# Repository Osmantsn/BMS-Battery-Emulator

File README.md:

# BMS-Test-Battery-Emulator
Hardware-based battery emulator for safe BMS testing. ESP32-S3 host controls up to 4 cell boards via I²C (AD5282), reads voltage/current/temperature through a multiplexer (ADG706), and provides a simple GUI/control interface.

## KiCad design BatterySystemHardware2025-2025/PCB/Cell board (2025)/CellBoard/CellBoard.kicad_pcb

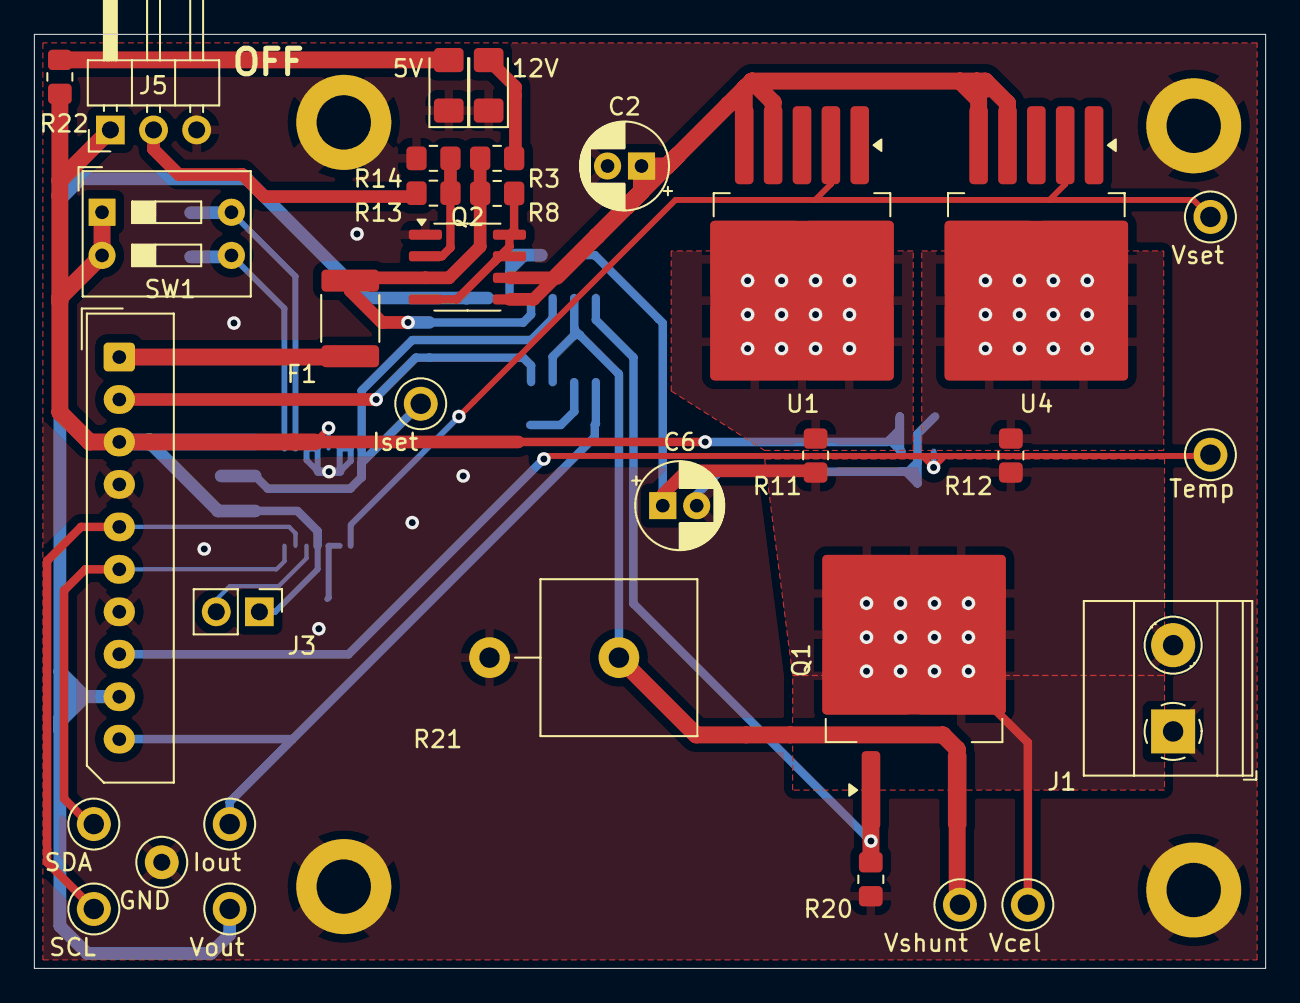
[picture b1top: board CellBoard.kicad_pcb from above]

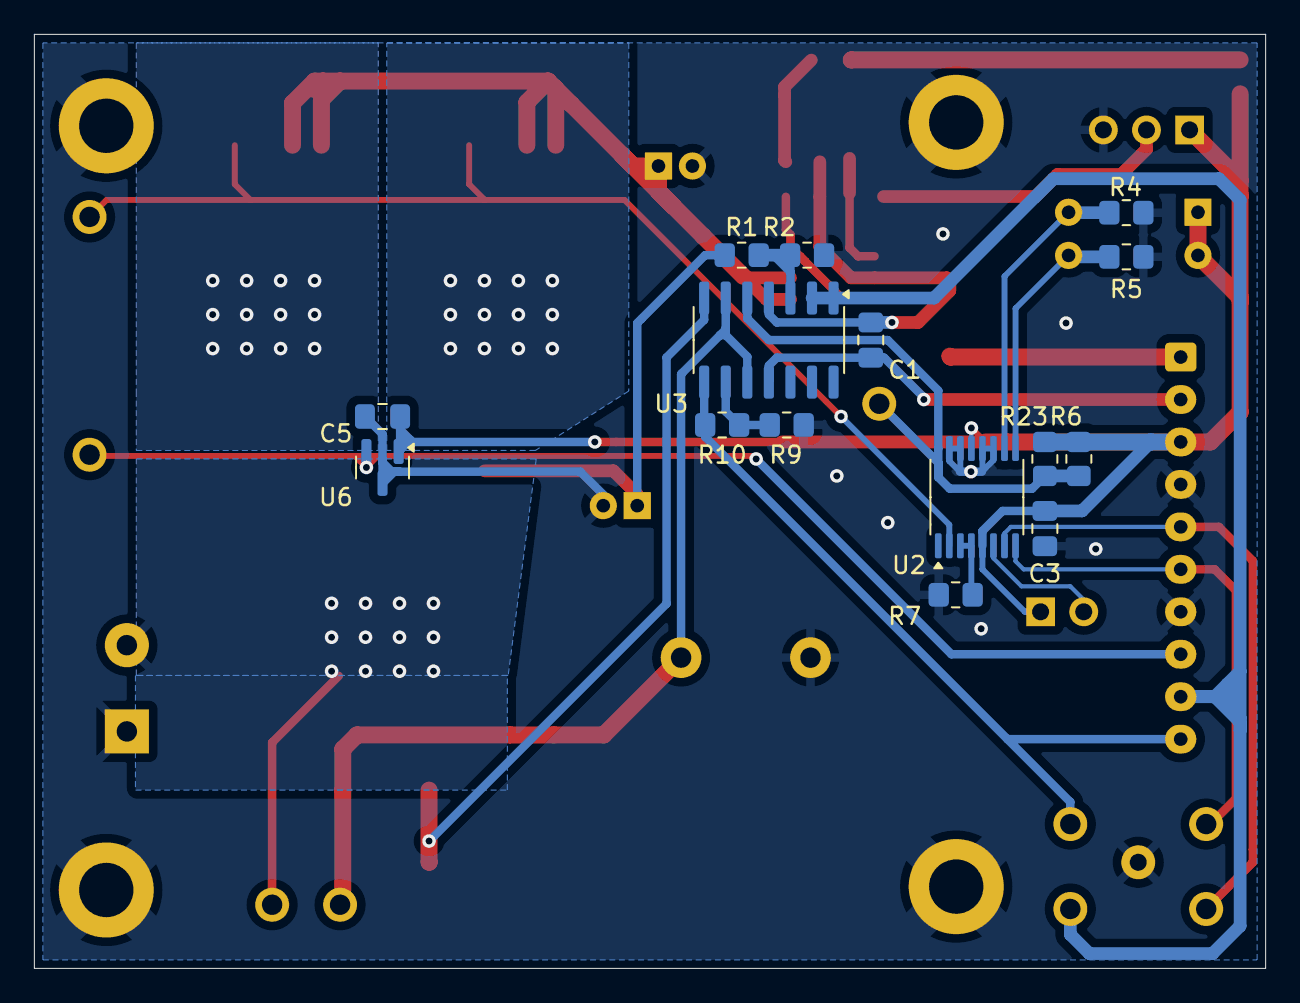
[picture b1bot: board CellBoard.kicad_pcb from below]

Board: 2 copper layers, 72.5 x 55.0 mm, 52 parts (15 on the bottom side), 29 nets.

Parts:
5V, 12V: LED; LED_1206_3216Metric_Pad1.42x1.75mm_HandSolder
C1, C3, C5: 100n; C_0805_2012Metric_Pad1.18x1.45mm_HandSolder
C2: 1u; CP_Radial_D5.0mm_P2.00mm
C6: 10u; CP_Radial_D5.0mm_P2.00mm
F1: 1812L200/12DR; Fuse_1812_4532Metric_Pad1.30x3.40mm_HandSolder
GND: TestPoint; TestPoint_Loop_D2.50mm_Drill1.0mm
H5, H6, H7, H8: MountingHole_Pad; MountingHole_3.2mm_M3_DIN965_Pad
Iout: TestPoint; TestPoint_Loop_D2.50mm_Drill1.0mm
Iset: TestPoint; TestPoint_Loop_D2.50mm_Drill1.0mm
J1: Screw_Terminal_01x02; TerminalBlock_Phoenix_MKDS-1,5-2-5.08_1x02_P5.08mm_Horizont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
J2: Conn_01x10_Pin; Molex_SPOX_5267-10A_1x10_P2.50mm_Vertical
J3: Conn_01x02_Pin; PinHeader_1x02_P2.54mm_Vertical
J5: Conn_01x03_Pin; PinHeader_1x03_P2.54mm_Horizontal
Q1: IRFS4115; TO-263-2
Q2: FDS4897C; SOIC-8_3.9x4.9mm_P1.27mm
R1: 1k2; R_0805_2012Metric_Pad1.20x1.40mm_HandSolder
R2: 2k7; R_0805_2012Metric_Pad1.20x1.40mm_HandSolder
R3: 390; R_0805_2012Metric_Pad1.20x1.40mm_HandSolder
R4, R5, R9, R13: 1k; R_0805_2012Metric_Pad1.20x1.40mm_HandSolder
R6, R23: 1M2; R_0805_2012Metric_Pad1.20x1.40mm_HandSolder
R7: 39k; R_0805_2012Metric_Pad1.20x1.40mm_HandSolder
R8, R14, R20: 10k; R_0805_2012Metric_Pad1.20x1.40mm_HandSolder
R10: 2k2; R_0805_2012Metric_Pad1.20x1.40mm_HandSolder
R11, R12: 10m; R_0805_2012Metric_Pad1.20x1.40mm_HandSolder
R21: 0.5; R_Axial_Power_L25.0mm_W9.0mm_P7.62mm_Vertical
R22: 120; R_0805_2012Metric_Pad1.20x1.40mm_HandSolder
SCL: TestPoint; TestPoint_Loop_D2.50mm_Drill1.0mm
SDA: TestPoint; TestPoint_Loop_D2.50mm_Drill1.0mm
SW1: BSE02GR; SW_DIP_SPSTx02_Slide_9.78x7.26mm_W7.62mm_P2.54mm
Temp: TestPoint; TestPoint_Loop_D2.50mm_Drill1.0mm
U1, U4: LT3080xQ; TO-263-5_TabPin3
U2: AD5282; TSSOP-16_4.4x5mm_P0.65mm
U3: TL084; SO-14_3.9x8.65mm_P1.27mm
U6: MCP9700Ax-ETT; SOT-23
Vcel: TestPoint; TestPoint_Loop_D2.50mm_Drill1.0mm
Vout: TestPoint; TestPoint_Loop_D2.50mm_Drill1.0mm
Vset: TestPoint; TestPoint_Loop_D2.50mm_Drill1.0mm
Vshunt: TestPoint; TestPoint_Loop_D2.50mm_Drill1.0mm

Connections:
+5V: C3.1, C5.1, J2.3, J3.1, J5.1, R6.2, R22.2, R23.2, SW1.1, SW1.2, U2.5 (VDD), U2.13 (VLOG), U6.1 (V_{DD})
+12V: C1.1, F1.1, Q2.3 (1), R3.2, R8.2, U3.4 (V+)
-12V: C1.2, J2.2, U3.11 (V-)
/A0: R5.2, SW1.3, U2.9 (AD0)
/A1: R4.2, SW1.4, U2.10 (AD1)
/VcontrolledOut: C6.1, J1.2, Q1.2 (D), R1.1, R11.2, R12.2, Vcel.1
/vShunt: Q1.3 (S), R21.1, U3.6 (-), U3.10 (+), Vshunt.1
CurrentController: Iout.1, J2.10, R10.2, U3.8
GND: 5V.1 (K), 12V.1 (K), C2.2, C3.2, C5.2, C6.2, GND.1, H5.1, H6.1, H7.1, H8.1, J1.1, J2.4, J2.7, J5.3, Q2.1 (S), R2.2, R4.1, R5.1, R7.1, R9.2, R14.2, R20.2, R21.2, U2.11 (GND), U2.12 (VSS), U2.14 (B2), U2.15 (W2), U6.3 (GND)
I2C_SCL: J2.5, SCL.1, U2.7 (SCL)
I2C_SDA: J2.6, SDA.1, U2.8 (SDA)
unnamed: 12V.2 (A), R3.1
unnamed: 5V.2 (A), R22.1
unnamed: F1.2, J2.1
unnamed: J3.2, U2.6 (~SHDN)
unnamed: J5.2, R13.1
unnamed: Q1.1 (G), R20.1, U3.7
unnamed: Q2.2 (G), R13.2, R14.1
unnamed: Q2.4 (G), Q2.7 (D), Q2.8 (D), R8.1
unnamed: R11.1, U1.3 (OUT)
unnamed: R12.1, U4.3 (OUT)
unnamed: C2.1, Q2.5 (D), Q2.6 (D), U1.4 (V_{CONTROL}), U1.5 (IN), U4.4 (V_{CONTROL}), U4.5 (IN)
unnamed: U1.2 (SET), U2.2 (A1), U4.2 (SET), Vset.1
unnamed: Iset.1, R6.1, R23.1, U2.16 (A2), U3.5 (+)
unnamed: R7.2, U2.3 (W1), U2.4 (B1)
unnamed: R1.2, R2.1, U3.3 (+)
unnamed: R9.1, R10.1, U3.9 (-)
TempCell: J2.8, Temp.1, U6.2 (V_{OUT})
VoltageController: J2.9, U3.1, U3.2 (-), Vout.1

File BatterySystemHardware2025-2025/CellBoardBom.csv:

Id;Designator;Footprint;Quantity;Designation;Supplier and ref;Order code
1;U4,U1;TO-263-5_TabPin3;2;LT3080xQ;nl.farnell.com;4027648
2;F1;Fuse_1812_4532Metric_Pad1.30x3.40mm_HandSolder;1;1812L200/12DR;nl.farnell.com;2786590
3;C6;CP_Radial_D5.0mm_P2.00mm;1;10u;;
4;R13,R4,R9,R5;R_0805_2012Metric_Pad1.20x1.40mm_HandSolder;4;1k;;
5;C2;CP_Radial_D5.0mm_P2.00mm;1;1u;;
6;R22;R_0805_2012Metric_Pad1.20x1.40mm_HandSolder;1;120;;
7;R20,R14,R8;R_0805_2012Metric_Pad1.20x1.40mm_HandSolder;3;10k;;
8;J3;PinHeader_1x02_P2.54mm_Vertical;1;Conn_01x02_Pin;;
9;R21;R_Axial_Power_L25.0mm_W9.0mm_P7.62mm_Vertical;1;0.5;;
10;Q1;TO-263-2;1;IRFS4115;nl.farnell.com;2725984
11;J2;Molex_SPOX_5267-10A_1x10_P2.50mm_Vertical;1;Conn_01x10_Pin;nl.farnell.com;3050985
12;J1;TerminalBlock_Phoenix_MKDS-1,5-2-5.08_1x02_P5.08mm_Horizontal;1;Screw_Terminal_01x02;;
13;12V,5V;LED_1206_3216Metric_Pad1.42x1.75mm_HandSolder;2;LED;;
14;R3;R_0805_2012Metric_Pad1.20x1.40mm_HandSolder;1;390;;
15;J5;PinHeader_1x03_P2.54mm_Horizontal;1;Conn_01x03_Pin;;
16;SW1;SW_DIP_SPSTx02_Slide_9.78x7.26mm_W7.62mm_P2.54mm;1;BSE02GR;nl.farnell.com;2864305
17;R11,R12;R_0805_2012Metric_Pad1.20x1.40mm_HandSolder;2;10m;;
18;Q2;SOIC-8_3.9x4.9mm_P1.27mm;1;FDS4897C;nl.farnell.com;2453864
19;R23,R6;R_0805_2012Metric_Pad1.20x1.40mm_HandSolder;2;1M2;;
20;U2;TSSOP-16_4.4x5mm_P0.65mm;1;AD5282;nl.farnell.com;4028680
21;R2;R_0805_2012Metric_Pad1.20x1.40mm_HandSolder;1;2k7;;
22;C1,C5,C3;C_0805_2012Metric_Pad1.18x1.45mm_HandSolder;3;100n;;
23;R1;R_0805_2012Metric_Pad1.20x1.40mm_HandSolder;1;1k2;;
24;U6;SOT-23;1;MCP9700Ax-ETT;nl.farnell.com;1605577
25;R10;R_0805_2012Metric_Pad1.20x1.40mm_HandSolder;1;2k2;;
26;U3;SO-14_3.9x8.65mm_P1.27mm;1;TL084;nl.farnell.com;1564346
27;R7;R_0805_2012Metric_Pad1.20x1.40mm_HandSolder;1;39k;;

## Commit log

2026-01-02 Update NewBMS_nextion_v2
2026-01-23 Update documentation / chapter 5 appendix
